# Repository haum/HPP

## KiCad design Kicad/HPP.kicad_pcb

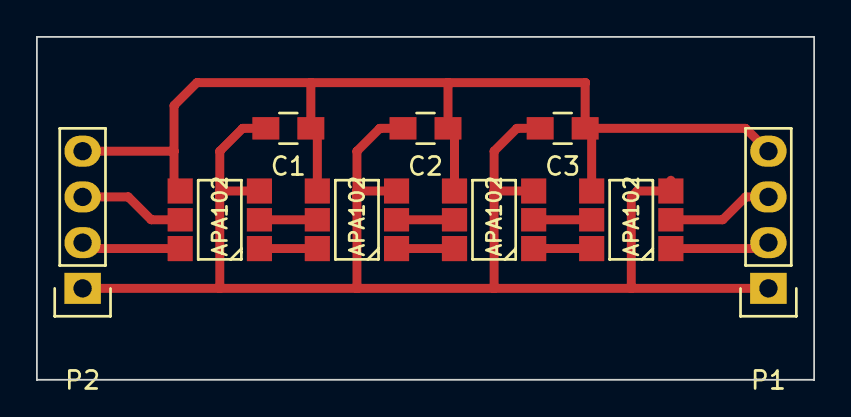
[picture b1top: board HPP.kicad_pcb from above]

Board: 2 copper layers, 43.2 x 19.0 mm, 9 parts (0 on the bottom side), 12 nets.

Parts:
C1, C2, C3: 100nF; C_0805_HandSoldering
P1, P2: CONN_4; Pin_Header_Straight_1x04
U1, U2, U3, U4: APA102

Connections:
unnamed: C1.1, C2.1, C3.1, P1.4, P2.4, U1.4, U2.4, U3.4, U4.4
unnamed: C1.2, C2.2, C3.2, P1.1, P2.1, U1.3, U2.3, U3.3, U4.3
unnamed: P1.2, U1.2
unnamed: P1.3, U1.1
unnamed: P2.2, U4.5
unnamed: P2.3, U4.6
unnamed: U1.5, U2.2
unnamed: U1.6, U2.1
unnamed: U2.5, U3.2
unnamed: U2.6, U3.1
unnamed: U3.5, U4.2
unnamed: U3.6, U4.1

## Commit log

2015-12-15 Projet Kicad
2015-12-15 Projet Freecad
2015-12-15 Rapport du projet
